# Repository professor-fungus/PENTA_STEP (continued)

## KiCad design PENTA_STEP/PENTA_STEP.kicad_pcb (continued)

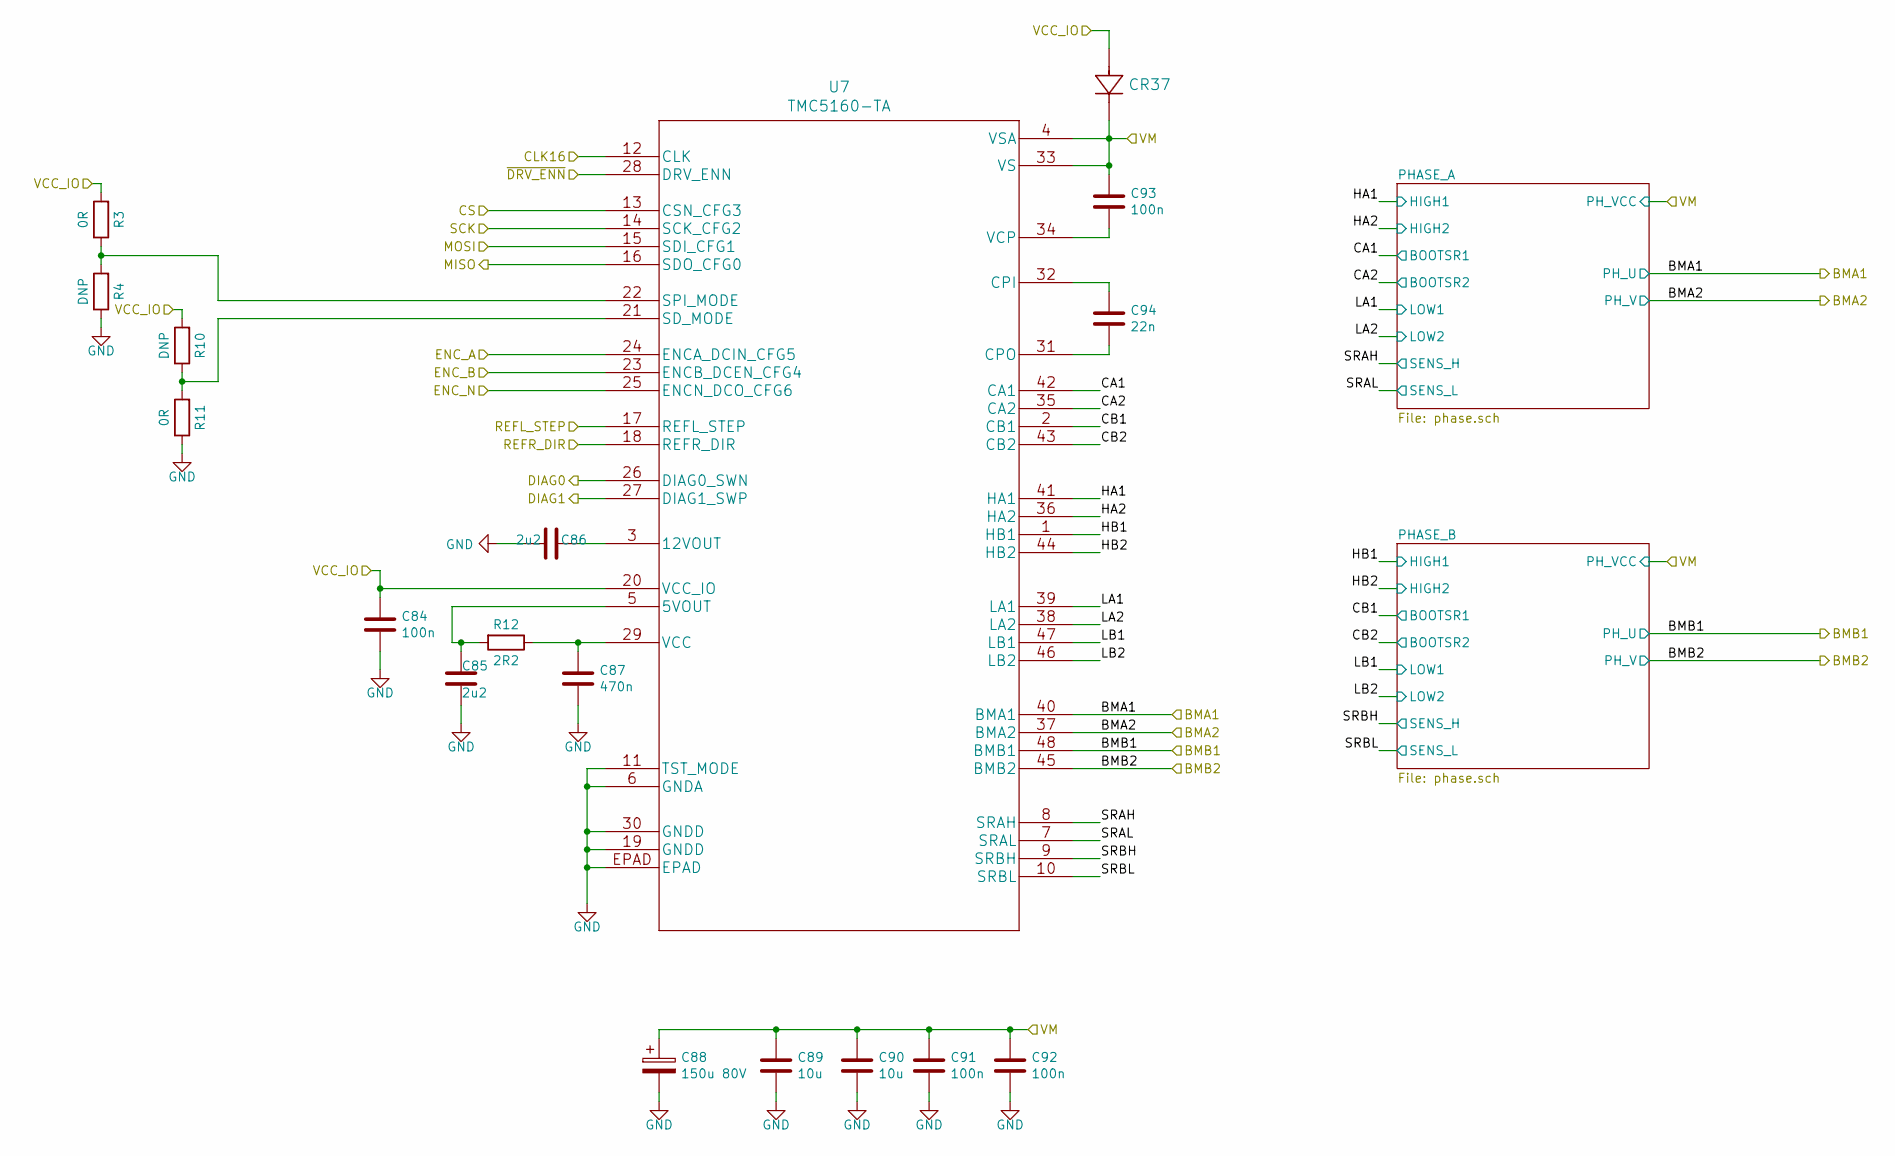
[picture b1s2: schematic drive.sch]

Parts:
C16, C23, C24, C25: 100n; C_0603_1608Metric_Pad1.05x0.95mm_HandSolder; MPN 06031C104KAT2A
C17, C18: 2u2; C_0603_1608Metric_Pad1.05x0.95mm_HandSolder; MPN CL10A225KO8NNNC
C19: 470n; C_0603_1608Metric_Pad1.05x0.95mm_HandSolder; MPN 885012106008
C20: 150u 80V; CAPAE1350X1400N_EEVFK1J151Q; MPN EEV-FK1K151Q
C21, C22: 10u; C_1210_3225Metric_Pad1.42x2.65mm_HandSolder; MPN C3225X7R1N106M250AC
C26: 22n; C_0603_1608Metric_Pad1.05x0.95mm_HandSolder; MPN CL10B223KB8NNNC
CR1: PMEG6010CEGWX; MPN S310FA
R86, R89: 0R; R_0603_1608Metric_Pad1.05x0.95mm_HandSolder; MPN RC0603JR-070RL
R87, R88: DNP; R_0603_1608Metric_Pad1.05x0.95mm_HandSolder; MPN RC0603JR-070RL
R90: 2R2; R_0603_1608Metric_Pad1.05x0.95mm_HandSolder; MPN RC0603FR-072R2L
U3: TMC5160-TA; MPN TMC5160-TA

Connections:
/DRIVE_1/BMA1: U3.40 (BMA1); also elsewhere on the board
/DRIVE_1/BMA2: U3.37 (BMA2); also elsewhere on the board
/DRIVE_1/BMB1: U3.48 (BMB1); also elsewhere on the board
/DRIVE_1/BMB2: U3.45 (BMB2); also elsewhere on the board
/DRIVE_1/CA1: U3.42 (CA1); also elsewhere on the board
/DRIVE_1/CA2: U3.35 (CA2); also elsewhere on the board
/DRIVE_1/CB1: U3.2 (CB1); also elsewhere on the board
/DRIVE_1/CB2: U3.43 (CB2); also elsewhere on the board
/DRIVE_1/CLK16: U3.12 (CLK); also elsewhere on the board
/DRIVE_1/CS: U3.13 (CSN_CFG3); also elsewhere on the board
/DRIVE_1/DIAG0: U3.26 (DIAG0_SWN); also elsewhere on the board
/DRIVE_1/DIAG1: U3.27 (DIAG1_SWP); also elsewhere on the board
/DRIVE_1/ENC_A: U3.24 (ENCA_DCIN_CFG5); also elsewhere on the board
/DRIVE_1/ENC_B: U3.23 (ENCB_DCEN_CFG4); also elsewhere on the board
/DRIVE_1/ENC_N: U3.25 (ENCN_DCO_CFG6); also elsewhere on the board
/DRIVE_1/HA1: U3.41 (HA1); also elsewhere on the board
/DRIVE_1/HA2: U3.36 (HA2); also elsewhere on the board
/DRIVE_1/HB1: U3.1 (HB1); also elsewhere on the board
/DRIVE_1/HB2: U3.44 (HB2); also elsewhere on the board
/DRIVE_1/LA1: U3.39 (LA1); also elsewhere on the board
/DRIVE_1/LA2: U3.38 (LA2); also elsewhere on the board
/DRIVE_1/LB1: U3.47 (LB1); also elsewhere on the board
/DRIVE_1/LB2: U3.46 (LB2); also elsewhere on the board
/DRIVE_1/MISO: U3.16 (SDO_CFG0); also elsewhere on the board
/DRIVE_1/MOSI: U3.15 (SDI_CFG1); also elsewhere on the board
/DRIVE_1/REFL_STEP: U3.17 (REFL_STEP); also elsewhere on the board
/DRIVE_1/REFR_DIR: U3.18 (REFR_DIR); also elsewhere on the board
/DRIVE_1/SCK: U3.14 (SCK_CFG2); also elsewhere on the board
/DRIVE_1/SRAH: U3.8 (SRAH); also elsewhere on the board
/DRIVE_1/SRAL: U3.7 (SRAL); also elsewhere on the board
/DRIVE_1/SRBH: U3.9 (SRBH); also elsewhere on the board
/DRIVE_1/SRBL: U3.10 (SRBL); also elsewhere on the board
/DRIVE_1/VCC_IO: C16.1, CR1.2, R86.2, R88.2, U3.20 (VCC_IO); also elsewhere on the board
/DRIVE_1/VM: C20.1, C21.1, C22.1, C23.1, C24.1, C25.1, CR1.1, U3.4 (VSA), U3.33 (VS); also elsewhere on the board
/DRIVE_1/~DRV_ENN: U3.28 (DRV_ENN); also elsewhere on the board
GND: C16.2, C17.1, C18.1, C19.2, C20.2, C21.2, C22.2, C23.2, C24.2, R87.1, R89.1, U3.6 (GNDA), U3.11 (TST_MODE), U3.19 (GNDD), U3.30 (GNDD), U3.EPAD; also elsewhere on the board
unnamed: C17.2, R90.2, U3.5 (5VOUT)
unnamed: C18.2, U3.3 (12VOUT)
unnamed: C19.1, R90.1, U3.29 (VCC)
unnamed: C25.2, U3.34 (VCP)
unnamed: C26.1, U3.32 (CPI)
unnamed: C26.2, U3.31 (CPO)
unnamed: R86.1, R87.2, U3.22 (SPI_MODE)
unnamed: R88.1, R89.2, U3.21 (SD_MODE)

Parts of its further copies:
C33, C40, C41, C42, C50, C57, C58, C59, C67, C74, C75, C76, C84, C91, C92, C93: 100n; C_0603_1608Metric_Pad1.05x0.95mm_HandSolder; MPN 06031C104KAT2A
C34, C35, C51, C52, C68, C69, C85, C86: 2u2; C_0603_1608Metric_Pad1.05x0.95mm_HandSolder; MPN CL10A225KO8NNNC
C36, C53, C70, C87: 470n; C_0603_1608Metric_Pad1.05x0.95mm_HandSolder; MPN 885012106008
C37, C54, C71, C88: 150u 80V; CAPAE1350X1400N_EEVFK1J151Q; MPN EEV-FK1K151Q
C38, C39, C55, C56, C72, C73, C89, C90: 10u; C_1210_3225Metric_Pad1.42x2.65mm_HandSolder; MPN C3225X7R1N106M250AC
C43, C60, C77, C94: 22n; C_0603_1608Metric_Pad1.05x0.95mm_HandSolder; MPN CL10B223KB8NNNC
CR10, CR19, CR28, CR37: PMEG6010CEGWX; MPN S310FA
R3, R11, R105, R108, R124, R127, R143, R146: 0R; R_0603_1608Metric_Pad1.05x0.95mm_HandSolder; MPN RC0603JR-070RL
R4, R10, R106, R107, R125, R126, R144, R145: DNP; R_0603_1608Metric_Pad1.05x0.95mm_HandSolder; MPN RC0603JR-070RL
R12, R109, R128, R147: 2R2; R_0603_1608Metric_Pad1.05x0.95mm_HandSolder; MPN RC0603FR-072R2L
U4, U5, U6, U7: TMC5160-TA; MPN TMC5160-TA

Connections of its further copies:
/DRIVE_2/BMA1: U4.40 (BMA1); also elsewhere on the board
/DRIVE_2/BMA2: U4.37 (BMA2); also elsewhere on the board
/DRIVE_2/BMB1: U4.48 (BMB1); also elsewhere on the board
/DRIVE_2/BMB2: U4.45 (BMB2); also elsewhere on the board
/DRIVE_2/CA1: U4.42 (CA1); also elsewhere on the board
/DRIVE_2/CA2: U4.35 (CA2); also elsewhere on the board
/DRIVE_2/CB1: U4.2 (CB1); also elsewhere on the board
/DRIVE_2/CB2: U4.43 (CB2); also elsewhere on the board
/DRIVE_2/CLK16: U4.12 (CLK); also elsewhere on the board
/DRIVE_2/CS: U4.13 (CSN_CFG3); also elsewhere on the board
/DRIVE_2/DIAG0: U4.26 (DIAG0_SWN); also elsewhere on the board
/DRIVE_2/DIAG1: U4.27 (DIAG1_SWP); also elsewhere on the board
/DRIVE_2/ENC_A: U4.24 (ENCA_DCIN_CFG5); also elsewhere on the board
/DRIVE_2/ENC_B: U4.23 (ENCB_DCEN_CFG4); also elsewhere on the board
/DRIVE_2/ENC_N: U4.25 (ENCN_DCO_CFG6); also elsewhere on the board
/DRIVE_2/HA1: U4.41 (HA1); also elsewhere on the board
/DRIVE_2/HA2: U4.36 (HA2); also elsewhere on the board
/DRIVE_2/HB1: U4.1 (HB1); also elsewhere on the board
/DRIVE_2/HB2: U4.44 (HB2); also elsewhere on the board
/DRIVE_2/LA1: U4.39 (LA1); also elsewhere on the board
/DRIVE_2/LA2: U4.38 (LA2); also elsewhere on the board
/DRIVE_2/LB1: U4.47 (LB1); also elsewhere on the board
/DRIVE_2/LB2: U4.46 (LB2); also elsewhere on the board
/DRIVE_2/MISO: U4.16 (SDO_CFG0); also elsewhere on the board
/DRIVE_2/MOSI: U4.15 (SDI_CFG1); also elsewhere on the board
/DRIVE_2/REFL_STEP: U4.17 (REFL_STEP); also elsewhere on the board
/DRIVE_2/REFR_DIR: U4.18 (REFR_DIR); also elsewhere on the board
/DRIVE_2/SCK: U4.14 (SCK_CFG2); also elsewhere on the board
/DRIVE_2/SRAH: U4.8 (SRAH); also elsewhere on the board
/DRIVE_2/SRAL: U4.7 (SRAL); also elsewhere on the board
/DRIVE_2/SRBH: U4.9 (SRBH); also elsewhere on the board
/DRIVE_2/SRBL: U4.10 (SRBL); also elsewhere on the board
/DRIVE_2/VCC_IO: C33.1, CR10.2, R105.2, R107.2, U4.20 (VCC_IO); also elsewhere on the board
/DRIVE_2/VM: C37.1, C38.1, C39.1, C40.1, C41.1, C42.1, CR10.1, U4.4 (VSA), U4.33 (VS); also elsewhere on the board
/DRIVE_2/~DRV_ENN: U4.28 (DRV_ENN); also elsewhere on the board
/DRIVE_3/BMA1: U5.40 (BMA1); also elsewhere on the board
/DRIVE_3/BMA2: U5.37 (BMA2); also elsewhere on the board
/DRIVE_3/BMB1: U5.48 (BMB1); also elsewhere on the board
/DRIVE_3/BMB2: U5.45 (BMB2); also elsewhere on the board
/DRIVE_3/CA1: U5.42 (CA1); also elsewhere on the board
/DRIVE_3/CA2: U5.35 (CA2); also elsewhere on the board
/DRIVE_3/CB1: U5.2 (CB1); also elsewhere on the board
/DRIVE_3/CB2: U5.43 (CB2); also elsewhere on the board
/DRIVE_3/CLK16: U5.12 (CLK); also elsewhere on the board
/DRIVE_3/CS: U5.13 (CSN_CFG3); also elsewhere on the board
/DRIVE_3/DIAG0: U5.26 (DIAG0_SWN); also elsewhere on the board
/DRIVE_3/DIAG1: U5.27 (DIAG1_SWP); also elsewhere on the board
/DRIVE_3/ENC_A: U5.24 (ENCA_DCIN_CFG5); also elsewhere on the board
/DRIVE_3/ENC_B: U5.23 (ENCB_DCEN_CFG4); also elsewhere on the board
/DRIVE_3/ENC_N: U5.25 (ENCN_DCO_CFG6); also elsewhere on the board
/DRIVE_3/HA1: U5.41 (HA1); also elsewhere on the board
/DRIVE_3/HA2: U5.36 (HA2); also elsewhere on the board
/DRIVE_3/HB1: U5.1 (HB1); also elsewhere on the board
/DRIVE_3/HB2: U5.44 (HB2); also elsewhere on the board
/DRIVE_3/LA1: U5.39 (LA1); also elsewhere on the board
/DRIVE_3/LA2: U5.38 (LA2); also elsewhere on the board
/DRIVE_3/LB1: U5.47 (LB1); also elsewhere on the board
/DRIVE_3/LB2: U5.46 (LB2); also elsewhere on the board
/DRIVE_3/MISO: U5.16 (SDO_CFG0); also elsewhere on the board
/DRIVE_3/MOSI: U5.15 (SDI_CFG1); also elsewhere on the board
/DRIVE_3/REFL_STEP: U5.17 (REFL_STEP); also elsewhere on the board
/DRIVE_3/REFR_DIR: U5.18 (REFR_DIR); also elsewhere on the board
/DRIVE_3/SCK: U5.14 (SCK_CFG2); also elsewhere on the board
/DRIVE_3/SRAH: U5.8 (SRAH); also elsewhere on the board
/DRIVE_3/SRAL: U5.7 (SRAL); also elsewhere on the board
/DRIVE_3/SRBH: U5.9 (SRBH); also elsewhere on the board
/DRIVE_3/SRBL: U5.10 (SRBL); also elsewhere on the board
/DRIVE_3/VCC_IO: C50.1, CR19.2, R124.2, R126.2, U5.20 (VCC_IO); also elsewhere on the board
/DRIVE_3/VM: C54.1, C55.1, C56.1, C57.1, C58.1, C59.1, CR19.1, U5.4 (VSA), U5.33 (VS); also elsewhere on the board
/DRIVE_3/~DRV_ENN: U5.28 (DRV_ENN); also elsewhere on the board
/DRIVE_4/BMA1: U6.40 (BMA1); also elsewhere on the board
/DRIVE_4/BMA2: U6.37 (BMA2); also elsewhere on the board
/DRIVE_4/BMB1: U6.48 (BMB1); also elsewhere on the board
/DRIVE_4/BMB2: U6.45 (BMB2); also elsewhere on the board
/DRIVE_4/CA1: U6.42 (CA1); also elsewhere on the board
/DRIVE_4/CA2: U6.35 (CA2); also elsewhere on the board
/DRIVE_4/CB1: U6.2 (CB1); also elsewhere on the board
/DRIVE_4/CB2: U6.43 (CB2); also elsewhere on the board
/DRIVE_4/CLK16: U6.12 (CLK); also elsewhere on the board
/DRIVE_4/CS: U6.13 (CSN_CFG3); also elsewhere on the board
/DRIVE_4/DIAG0: U6.26 (DIAG0_SWN); also elsewhere on the board
/DRIVE_4/DIAG1: U6.27 (DIAG1_SWP); also elsewhere on the board
/DRIVE_4/ENC_A: U6.24 (ENCA_DCIN_CFG5); also elsewhere on the board
/DRIVE_4/ENC_B: U6.23 (ENCB_DCEN_CFG4); also elsewhere on the board
/DRIVE_4/ENC_N: U6.25 (ENCN_DCO_CFG6); also elsewhere on the board
/DRIVE_4/HA1: U6.41 (HA1); also elsewhere on the board
/DRIVE_4/HA2: U6.36 (HA2); also elsewhere on the board
/DRIVE_4/HB1: U6.1 (HB1); also elsewhere on the board
/DRIVE_4/HB2: U6.44 (HB2); also elsewhere on the board
/DRIVE_4/LA1: U6.39 (LA1); also elsewhere on the board
/DRIVE_4/LA2: U6.38 (LA2); also elsewhere on the board
/DRIVE_4/LB1: U6.47 (LB1); also elsewhere on the board
/DRIVE_4/LB2: U6.46 (LB2); also elsewhere on the board
/DRIVE_4/MISO: U6.16 (SDO_CFG0); also elsewhere on the board
/DRIVE_4/MOSI: U6.15 (SDI_CFG1); also elsewhere on the board
/DRIVE_4/REFL_STEP: U6.17 (REFL_STEP); also elsewhere on the board
/DRIVE_4/REFR_DIR: U6.18 (REFR_DIR); also elsewhere on the board
/DRIVE_4/SCK: U6.14 (SCK_CFG2); also elsewhere on the board
/DRIVE_4/SRAH: U6.8 (SRAH); also elsewhere on the board
/DRIVE_4/SRAL: U6.7 (SRAL); also elsewhere on the board
/DRIVE_4/SRBH: U6.9 (SRBH); also elsewhere on the board
/DRIVE_4/SRBL: U6.10 (SRBL); also elsewhere on the board
/DRIVE_4/VCC_IO: C67.1, CR28.2, R143.2, R145.2, U6.20 (VCC_IO); also elsewhere on the board
/DRIVE_4/VM: C71.1, C72.1, C73.1, C74.1, C75.1, C76.1, CR28.1, U6.4 (VSA), U6.33 (VS); also elsewhere on the board
/DRIVE_4/~DRV_ENN: U6.28 (DRV_ENN); also elsewhere on the board
/DRIVE_5/BMA1: U7.40 (BMA1); also elsewhere on the board
/DRIVE_5/BMA2: U7.37 (BMA2); also elsewhere on the board
/DRIVE_5/BMB1: U7.48 (BMB1); also elsewhere on the board
/DRIVE_5/BMB2: U7.45 (BMB2); also elsewhere on the board
/DRIVE_5/CA1: U7.42 (CA1); also elsewhere on the board
/DRIVE_5/CA2: U7.35 (CA2); also elsewhere on the board
/DRIVE_5/CB1: U7.2 (CB1); also elsewhere on the board
/DRIVE_5/CB2: U7.43 (CB2); also elsewhere on the board
/DRIVE_5/CLK16: U7.12 (CLK); also elsewhere on the board
/DRIVE_5/CS: U7.13 (CSN_CFG3); also elsewhere on the board
/DRIVE_5/DIAG0: U7.26 (DIAG0_SWN); also elsewhere on the board
/DRIVE_5/DIAG1: U7.27 (DIAG1_SWP); also elsewhere on the board
/DRIVE_5/ENC_A: U7.24 (ENCA_DCIN_CFG5); also elsewhere on the board
/DRIVE_5/ENC_B: U7.23 (ENCB_DCEN_CFG4); also elsewhere on the board
/DRIVE_5/ENC_N: U7.25 (ENCN_DCO_CFG6); also elsewhere on the board
/DRIVE_5/HA1: U7.41 (HA1); also elsewhere on the board
/DRIVE_5/HA2: U7.36 (HA2); also elsewhere on the board
/DRIVE_5/HB1: U7.1 (HB1); also elsewhere on the board
/DRIVE_5/HB2: U7.44 (HB2); also elsewhere on the board
/DRIVE_5/LA1: U7.39 (LA1); also elsewhere on the board
/DRIVE_5/LA2: U7.38 (LA2); also elsewhere on the board
/DRIVE_5/LB1: U7.47 (LB1); also elsewhere on the board
/DRIVE_5/LB2: U7.46 (LB2); also elsewhere on the board
/DRIVE_5/MISO: U7.16 (SDO_CFG0); also elsewhere on the board
/DRIVE_5/MOSI: U7.15 (SDI_CFG1); also elsewhere on the board
/DRIVE_5/REFL_STEP: U7.17 (REFL_STEP); also elsewhere on the board
/DRIVE_5/REFR_DIR: U7.18 (REFR_DIR); also elsewhere on the board
/DRIVE_5/SCK: U7.14 (SCK_CFG2); also elsewhere on the board
/DRIVE_5/SRAH: U7.8 (SRAH); also elsewhere on the board
/DRIVE_5/SRAL: U7.7 (SRAL); also elsewhere on the board
/DRIVE_5/SRBH: U7.9 (SRBH); also elsewhere on the board
/DRIVE_5/SRBL: U7.10 (SRBL); also elsewhere on the board
/DRIVE_5/VCC_IO: C84.1, CR37.2, R3.2, R10.2, U7.20 (VCC_IO); also elsewhere on the board
/DRIVE_5/VM: C88.1, C89.1, C90.1, C91.1, C92.1, C93.1, CR37.1, U7.4 (VSA), U7.33 (VS); also elsewhere on the board
/DRIVE_5/~DRV_ENN: U7.28 (DRV_ENN); also elsewhere on the board
GND: C33.2, C34.1, C35.1, C36.2, C37.2, C38.2, C39.2, C40.2, C41.2, C50.2, C51.1, C52.1, C53.2, C54.2, C55.2, C56.2, C57.2, C58.2, C67.2, C68.1, C69.1, C70.2, C71.2, C72.2, C73.2, C74.2, C75.2, C84.2, C85.1, C86.1, C87.2, C88.2, C89.2, C90.2, C91.2, C92.2, R4.1, R11.1, R106.1, R108.1, R125.1, R127.1, R144.1, R146.1, U4.6 (GNDA), U4.11 (TST_MODE), U4.19 (GNDD), U4.30 (GNDD), U4.EPAD, U5.6 (GNDA), U5.11 (TST_MODE), U5.19 (GNDD), U5.30 (GNDD), U5.EPAD, U6.6 (GNDA), U6.11 (TST_MODE), U6.19 (GNDD), U6.30 (GNDD), U6.EPAD, U7.6 (GNDA), U7.11 (TST_MODE), U7.19 (GNDD), U7.30 (GNDD), U7.EPAD; also elsewhere on the board
unnamed: C34.2, R109.2, U4.5 (5VOUT)
unnamed: C35.2, U4.3 (12VOUT)
unnamed: C36.1, R109.1, U4.29 (VCC)
unnamed: C42.2, U4.34 (VCP)
unnamed: C43.1, U4.32 (CPI)
unnamed: C43.2, U4.31 (CPO)
unnamed: C51.2, R128.2, U5.5 (5VOUT)
unnamed: C52.2, U5.3 (12VOUT)
unnamed: C53.1, R128.1, U5.29 (VCC)
unnamed: C59.2, U5.34 (VCP)
unnamed: C60.1, U5.32 (CPI)
unnamed: C60.2, U5.31 (CPO)
unnamed: C68.2, R147.2, U6.5 (5VOUT)
unnamed: C69.2, U6.3 (12VOUT)
unnamed: C70.1, R147.1, U6.29 (VCC)
unnamed: C76.2, U6.34 (VCP)
unnamed: C77.1, U6.32 (CPI)
unnamed: C77.2, U6.31 (CPO)
unnamed: C85.2, R12.2, U7.5 (5VOUT)
unnamed: C86.2, U7.3 (12VOUT)
unnamed: C87.1, R12.1, U7.29 (VCC)
unnamed: C93.2, U7.34 (VCP)
unnamed: C94.1, U7.32 (CPI)
unnamed: C94.2, U7.31 (CPO)
unnamed: R3.1, R4.2, U7.22 (SPI_MODE)
unnamed: R10.1, R11.2, U7.21 (SD_MODE)
unnamed: R105.1, R106.2, U4.22 (SPI_MODE)
unnamed: R107.1, R108.2, U4.21 (SD_MODE)
unnamed: R124.1, R125.2, U5.22 (SPI_MODE)
unnamed: R126.1, R127.2, U5.21 (SD_MODE)
unnamed: R143.1, R144.2, U6.22 (SPI_MODE)
unnamed: R145.1, R146.2, U6.21 (SD_MODE)

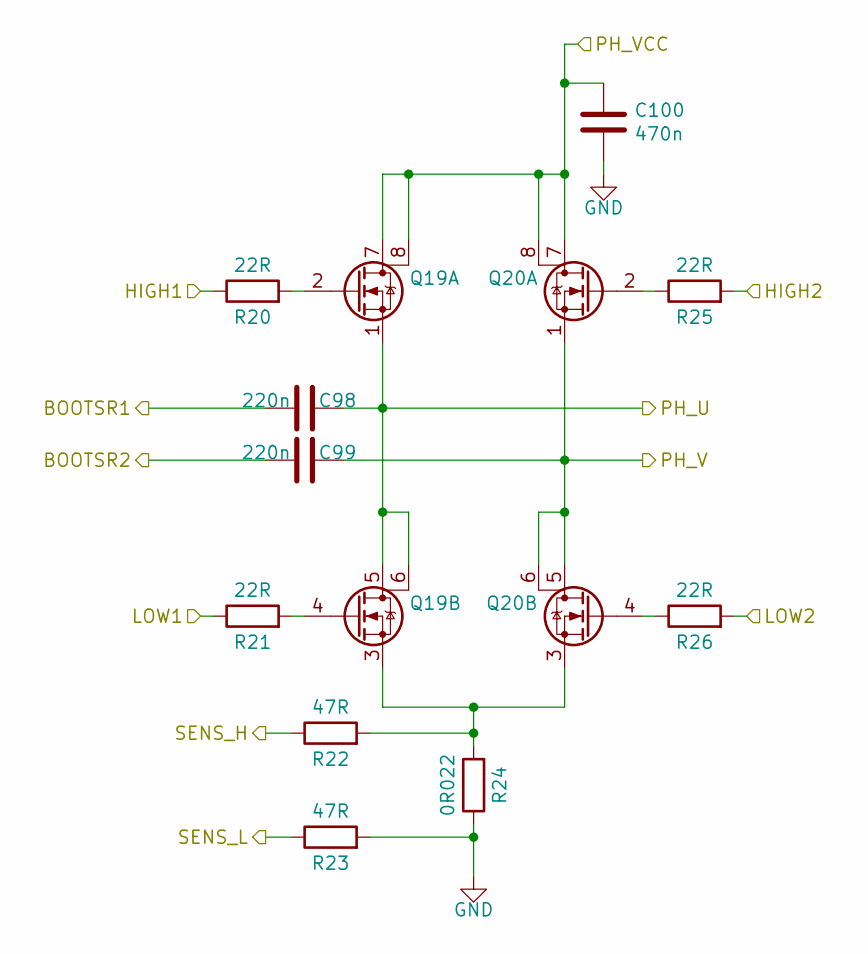
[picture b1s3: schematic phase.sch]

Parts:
C27, C28: 220n; C_0603_1608Metric_Pad1.05x0.95mm_HandSolder; MPN CL10F224ZB8NNNC
C29: 470n; C_0603_1608Metric_Pad1.05x0.95mm_HandSolder; MPN 885012106008
Q1, Q2: BUK9K45-100E,115; TRANS_BUK7K12-60EX; MPN BUK9K45-100E,115
R91, R92, R96, R97: 22R; R_0603_1608Metric_Pad1.05x0.95mm_HandSolder; MPN ERJ-3EKF22R0V
R93, R94: 47R; R_0603_1608Metric_Pad1.05x0.95mm_HandSolder; MPN CRGCQ0603F47R
R95: 0R022; WSH2818R0500FEA; MPN WSHM2818R0220FEA

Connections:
/DRIVE_1/BMA1: C27.1, Q1.1 (S), Q1.5 (D2), Q1.6 (D2); also elsewhere on the board
/DRIVE_1/BMA2: C28.1, Q2.1 (S), Q2.5 (D2), Q2.6 (D2); also elsewhere on the board
/DRIVE_1/CA1: C27.2; also elsewhere on the board
/DRIVE_1/CA2: C28.2; also elsewhere on the board
/DRIVE_1/HA1: R91.1; also elsewhere on the board
/DRIVE_1/HA2: R96.2; also elsewhere on the board
/DRIVE_1/LA1: R92.1; also elsewhere on the board
/DRIVE_1/LA2: R97.2; also elsewhere on the board
/DRIVE_1/SRAH: R93.1; also elsewhere on the board
/DRIVE_1/SRAL: R94.1; also elsewhere on the board
/DRIVE_1/VM: C29.1, Q1.7 (D2), Q1.8 (D2), Q2.7 (D2), Q2.8 (D2); also elsewhere on the board
GND: C29.2, R94.2, R95.1; also elsewhere on the board
unnamed: Q1.2 (G), R91.2
unnamed: Q1.3 (S), Q2.3 (S), R93.2, R95.2
unnamed: Q1.4 (G), R92.2
unnamed: Q2.2 (G), R96.1
unnamed: Q2.4 (G), R97.1

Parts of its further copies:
C30, C31, C44, C45, C47, C48, C61, C62, C64, C65, C78, C79, C81, C82, C95, C96, C98, C99: 220n; C_0603_1608Metric_Pad1.05x0.95mm_HandSolder; MPN CL10F224ZB8NNNC
C32, C46, C49, C63, C66, C80, C83, C97, C100: 470n; C_0603_1608Metric_Pad1.05x0.95mm_HandSolder; MPN 885012106008
Q3, Q4, Q5, Q6, Q7, Q8, Q9, Q10, Q11, Q12, Q13, Q14, Q15, Q16, Q17, Q18, Q19, Q20: BUK9K45-100E,115; TRANS_BUK7K12-60EX; MPN BUK9K45-100E,115
R13, R14, R18, R19, R20, R21, R25, R26, R98, R99, R103, R104, R110, R111, R115, R116, R117, R118, R122, R123, R129, R130, R134, R135, R136, R137, R141, R142, R148, R149, R153, R154, R155, R156, R160, R161: 22R; R_0603_1608Metric_Pad1.05x0.95mm_HandSolder; MPN ERJ-3EKF22R0V
R15, R16, R22, R23, R100, R101, R112, R113, R119, R120, R131, R132, R138, R139, R150, R151, R157, R158: 47R; R_0603_1608Metric_Pad1.05x0.95mm_HandSolder; MPN CRGCQ0603F47R
R17, R24, R102, R114, R121, R133, R140, R152, R159: 0R022; WSH2818R0500FEA; MPN WSHM2818R0220FEA

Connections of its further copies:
/DRIVE_1/BMB1: C30.1, Q3.1 (S), Q3.5 (D2), Q3.6 (D2); also elsewhere on the board
/DRIVE_1/BMB2: C31.1, Q4.1 (S), Q4.5 (D2), Q4.6 (D2); also elsewhere on the board
/DRIVE_1/CB1: C30.2; also elsewhere on the board
/DRIVE_1/CB2: C31.2; also elsewhere on the board
/DRIVE_1/HB1: R98.1; also elsewhere on the board
/DRIVE_1/HB2: R103.2; also elsewhere on the board
/DRIVE_1/LB1: R99.1; also elsewhere on the board
/DRIVE_1/LB2: R104.2; also elsewhere on the board
/DRIVE_1/SRBH: R100.1; also elsewhere on the board
/DRIVE_1/SRBL: R101.1; also elsewhere on the board
/DRIVE_1/VM: C32.1, Q3.7 (D2), Q3.8 (D2), Q4.7 (D2), Q4.8 (D2); also elsewhere on the board
/DRIVE_2/BMA1: C44.1, Q5.1 (S), Q5.5 (D2), Q5.6 (D2); also elsewhere on the board
/DRIVE_2/BMA2: C45.1, Q6.1 (S), Q6.5 (D2), Q6.6 (D2); also elsewhere on the board
/DRIVE_2/BMB1: C47.1, Q7.1 (S), Q7.5 (D2), Q7.6 (D2); also elsewhere on the board
/DRIVE_2/BMB2: C48.1, Q8.1 (S), Q8.5 (D2), Q8.6 (D2); also elsewhere on the board
/DRIVE_2/CA1: C44.2; also elsewhere on the board
/DRIVE_2/CA2: C45.2; also elsewhere on the board
/DRIVE_2/CB1: C47.2; also elsewhere on the board
/DRIVE_2/CB2: C48.2; also elsewhere on the board
/DRIVE_2/HA1: R110.1; also elsewhere on the board
/DRIVE_2/HA2: R115.2; also elsewhere on the board
/DRIVE_2/HB1: R117.1; also elsewhere on the board
/DRIVE_2/HB2: R122.2; also elsewhere on the board
/DRIVE_2/LA1: R111.1; also elsewhere on the board
/DRIVE_2/LA2: R116.2; also elsewhere on the board
/DRIVE_2/LB1: R118.1; also elsewhere on the board
/DRIVE_2/LB2: R123.2; also elsewhere on the board
/DRIVE_2/SRAH: R112.1; also elsewhere on the board
/DRIVE_2/SRAL: R113.1; also elsewhere on the board
/DRIVE_2/SRBH: R119.1; also elsewhere on the board
/DRIVE_2/SRBL: R120.1; also elsewhere on the board
/DRIVE_2/VM: C46.1, C49.1, Q5.7 (D2), Q5.8 (D2), Q6.7 (D2), Q6.8 (D2), Q7.7 (D2), Q7.8 (D2), Q8.7 (D2), Q8.8 (D2); also elsewhere on the board
/DRIVE_3/BMA1: C61.1, Q9.1 (S), Q9.5 (D2), Q9.6 (D2); also elsewhere on the board
/DRIVE_3/BMA2: C62.1, Q10.1 (S), Q10.5 (D2), Q10.6 (D2); also elsewhere on the board
/DRIVE_3/BMB1: C64.1, Q11.1 (S), Q11.5 (D2), Q11.6 (D2); also elsewhere on the board
/DRIVE_3/BMB2: C65.1, Q12.1 (S), Q12.5 (D2), Q12.6 (D2); also elsewhere on the board
/DRIVE_3/CA1: C61.2; also elsewhere on the board
/DRIVE_3/CA2: C62.2; also elsewhere on the board
/DRIVE_3/CB1: C64.2; also elsewhere on the board
/DRIVE_3/CB2: C65.2; also elsewhere on the board
/DRIVE_3/HA1: R129.1; also elsewhere on the board
/DRIVE_3/HA2: R134.2; also elsewhere on the board
/DRIVE_3/HB1: R136.1; also elsewhere on the board
/DRIVE_3/HB2: R141.2; also elsewhere on the board
/DRIVE_3/LA1: R130.1; also elsewhere on the board
/DRIVE_3/LA2: R135.2; also elsewhere on the board
/DRIVE_3/LB1: R137.1; also elsewhere on the board
/DRIVE_3/LB2: R142.2; also elsewhere on the board
/DRIVE_3/SRAH: R131.1; also elsewhere on the board
/DRIVE_3/SRAL: R132.1; also elsewhere on the board
/DRIVE_3/SRBH: R138.1; also elsewhere on the board
/DRIVE_3/SRBL: R139.1; also elsewhere on the board
/DRIVE_3/VM: C63.1, C66.1, Q9.7 (D2), Q9.8 (D2), Q10.7 (D2), Q10.8 (D2), Q11.7 (D2), Q11.8 (D2), Q12.7 (D2), Q12.8 (D2); also elsewhere on the board
/DRIVE_4/BMA1: C78.1, Q13.1 (S), Q13.5 (D2), Q13.6 (D2); also elsewhere on the board
/DRIVE_4/BMA2: C79.1, Q14.1 (S), Q14.5 (D2), Q14.6 (D2); also elsewhere on the board
/DRIVE_4/BMB1: C81.1, Q15.1 (S), Q15.5 (D2), Q15.6 (D2); also elsewhere on the board
/DRIVE_4/BMB2: C82.1, Q16.1 (S), Q16.5 (D2), Q16.6 (D2); also elsewhere on the board
/DRIVE_4/CA1: C78.2; also elsewhere on the board
/DRIVE_4/CA2: C79.2; also elsewhere on the board
/DRIVE_4/CB1: C81.2; also elsewhere on the board
/DRIVE_4/CB2: C82.2; also elsewhere on the board
/DRIVE_4/HA1: R148.1; also elsewhere on the board
/DRIVE_4/HA2: R153.2; also elsewhere on the board
/DRIVE_4/HB1: R155.1; also elsewhere on the board
/DRIVE_4/HB2: R160.2; also elsewhere on the board
/DRIVE_4/LA1: R149.1; also elsewhere on the board
/DRIVE_4/LA2: R154.2; also elsewhere on the board
/DRIVE_4/LB1: R156.1; also elsewhere on the board
/DRIVE_4/LB2: R161.2; also elsewhere on the board
/DRIVE_4/SRAH: R150.1; also elsewhere on the board
/DRIVE_4/SRAL: R151.1; also elsewhere on the board
/DRIVE_4/SRBH: R157.1; also elsewhere on the board
/DRIVE_4/SRBL: R158.1; also elsewhere on the board
/DRIVE_4/VM: C80.1, C83.1, Q13.7 (D2), Q13.8 (D2), Q14.7 (D2), Q14.8 (D2), Q15.7 (D2), Q15.8 (D2), Q16.7 (D2), Q16.8 (D2); also elsewhere on the board
/DRIVE_5/BMA1: C95.1, Q17.1 (S), Q17.5 (D2), Q17.6 (D2); also elsewhere on the board
/DRIVE_5/BMA2: C96.1, Q18.1 (S), Q18.5 (D2), Q18.6 (D2); also elsewhere on the board
/DRIVE_5/BMB1: C98.1, Q19.1 (S), Q19.5 (D2), Q19.6 (D2); also elsewhere on the board
/DRIVE_5/BMB2: C99.1, Q20.1 (S), Q20.5 (D2), Q20.6 (D2); also elsewhere on the board
/DRIVE_5/CA1: C95.2; also elsewhere on the board
/DRIVE_5/CA2: C96.2; also elsewhere on the board
/DRIVE_5/CB1: C98.2; also elsewhere on the board
/DRIVE_5/CB2: C99.2; also elsewhere on the board
/DRIVE_5/HA1: R13.1; also elsewhere on the board
/DRIVE_5/HA2: R18.2; also elsewhere on the board
/DRIVE_5/HB1: R20.1; also elsewhere on the board
/DRIVE_5/HB2: R25.2; also elsewhere on the board
/DRIVE_5/LA1: R14.1; also elsewhere on the board
/DRIVE_5/LA2: R19.2; also elsewhere on the board
/DRIVE_5/LB1: R21.1; also elsewhere on the board
/DRIVE_5/LB2: R26.2; also elsewhere on the board
/DRIVE_5/SRAH: R15.1; also elsewhere on the board
/DRIVE_5/SRAL: R16.1; also elsewhere on the board
/DRIVE_5/SRBH: R22.1; also elsewhere on the board
/DRIVE_5/SRBL: R23.1; also elsewhere on the board
/DRIVE_5/VM: C97.1, C100.1, Q17.7 (D2), Q17.8 (D2), Q18.7 (D2), Q18.8 (D2), Q19.7 (D2), Q19.8 (D2), Q20.7 (D2), Q20.8 (D2); also elsewhere on the board
GND: C32.2, C46.2, C49.2, C63.2, C66.2, C80.2, C83.2, C97.2, C100.2, R16.2, R17.1, R23.2, R24.1, R101.2, R102.1, R113.2, R114.1, R120.2, R121.1, R132.2, R133.1, R139.2, R140.1, R151.2, R152.1, R158.2, R159.1; also elsewhere on the board
unnamed: Q3.2 (G), R98.2
unnamed: Q3.3 (S), Q4.3 (S), R100.2, R102.2
unnamed: Q3.4 (G), R99.2
unnamed: Q4.2 (G), R103.1
unnamed: Q4.4 (G), R104.1
unnamed: Q5.2 (G), R110.2
unnamed: Q5.3 (S), Q6.3 (S), R112.2, R114.2
unnamed: Q5.4 (G), R111.2
unnamed: Q6.2 (G), R115.1
unnamed: Q6.4 (G), R116.1
unnamed: Q7.2 (G), R117.2
unnamed: Q7.3 (S), Q8.3 (S), R119.2, R121.2
unnamed: Q7.4 (G), R118.2
unnamed: Q8.2 (G), R122.1
unnamed: Q8.4 (G), R123.1
unnamed: Q9.2 (G), R129.2
unnamed: Q9.4 (G), R130.2
unnamed: Q10.2 (G), R134.1
unnamed: Q9.3 (S), Q10.3 (S), R131.2, R133.2
unnamed: Q10.4 (G), R135.1
unnamed: Q11.2 (G), R136.2
unnamed: Q11.3 (S), Q12.3 (S), R138.2, R140.2
unnamed: Q11.4 (G), R137.2
unnamed: Q12.2 (G), R141.1
unnamed: Q12.4 (G), R142.1
unnamed: Q13.2 (G), R148.2
unnamed: Q13.3 (S), Q14.3 (S), R150.2, R152.2
unnamed: Q13.4 (G), R149.2
unnamed: Q14.2 (G), R153.1
unnamed: Q14.4 (G), R154.1
unnamed: Q15.2 (G), R155.2
unnamed: Q15.3 (S), Q16.3 (S), R157.2, R159.2
unnamed: Q15.4 (G), R156.2
unnamed: Q16.2 (G), R160.1
unnamed: Q16.4 (G), R161.1
unnamed: Q17.2 (G), R13.2
unnamed: Q17.3 (S), Q18.3 (S), R15.2, R17.2
unnamed: Q17.4 (G), R14.2
unnamed: Q18.2 (G), R18.1
unnamed: Q18.4 (G), R19.1
unnamed: Q19.2 (G), R20.2
unnamed: Q19.3 (S), Q20.3 (S), R22.2, R24.2
unnamed: Q19.4 (G), R21.2
unnamed: Q20.2 (G), R25.1
unnamed: Q20.4 (G), R26.1

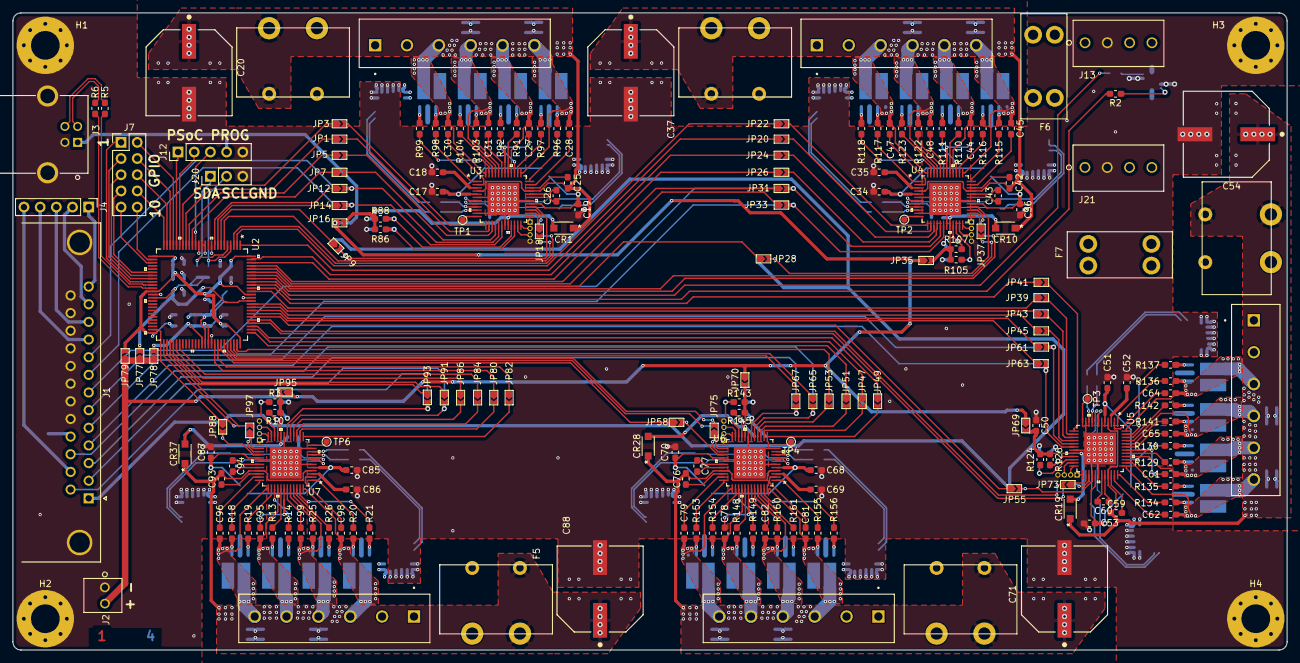
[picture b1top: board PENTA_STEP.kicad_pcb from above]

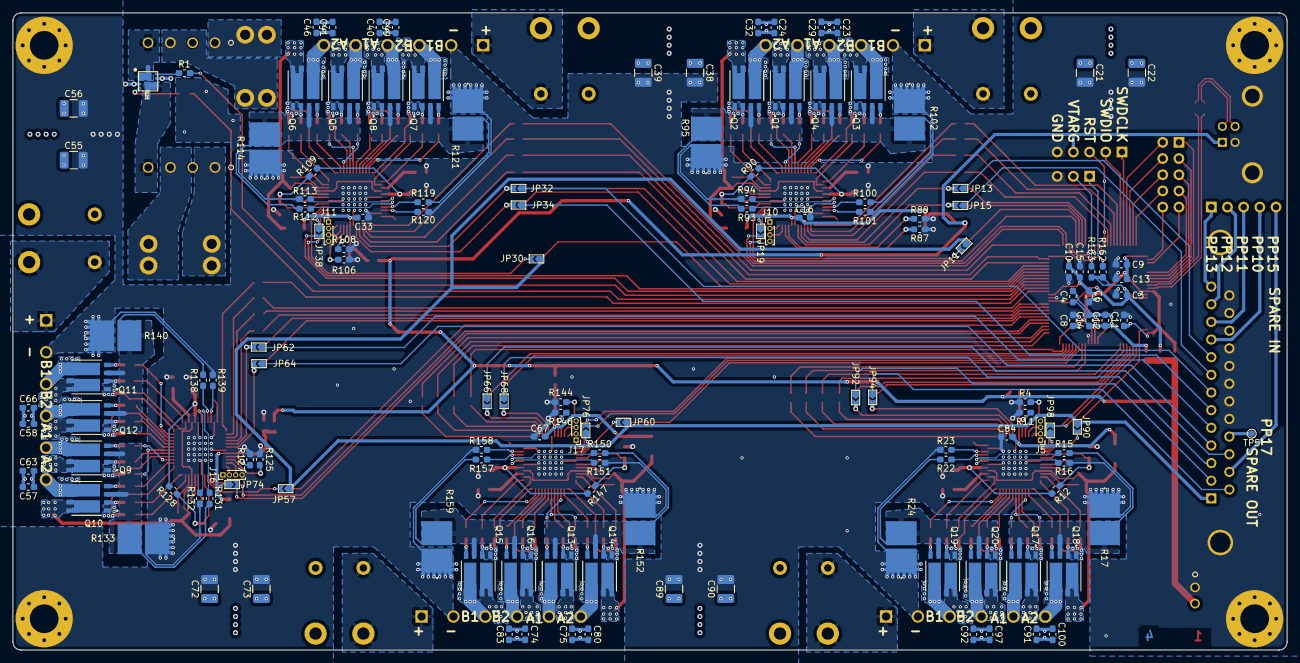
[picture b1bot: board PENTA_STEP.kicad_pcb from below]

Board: 4 copper layers, 200.0 x 100.0 mm, 333 parts (140 on the bottom side), 367 nets.

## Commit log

2019-12-26 rough BOM, have primary components.
2019-12-27 began H-bridge stage
2019-12-28 finished h bridges, converted to hierarchical layout
2019-12-30 added more components, fleshed out DB-25 interface, added PSoC
2020-01-05 many changes, fixed issue with hierarchical(sp?) pins
2020-01-09 beginning layout
2020-01-10 complebegan adding 3D files
2020-01-10 added some 3D files, converted to personal computer paths
2020-01-12 changed scope to 5 axis, preliminary completion of component positioning
2020-01-12 renaming to reflect 5 axes
2020-01-12 adding picture
2020-01-13 3D links buggered, tinkered with alternate placement of FETs
2020-01-19 corrected symbol and footprint paths
2020-01-19 progressing on layout
2020-01-21 V1 layout nearing completion
2020-01-22 Added two FET-controlled outputs to the board
2020-01-27 majority routed, eliminated ATTINY coprocessor
2020-01-29 completed preliminary routing, still need plane touchup
2020-02-02 finished layout, added top and bottom layer ground pours, added fuses for FET outputs
2020-02-02 finished layout, added top and bottom layer ground pours, added fuses for FET outputs, but forgot to save ;)
2020-02-25 finalized BOM, found TMC5160-TA being replaced by TMC5160A-TA
